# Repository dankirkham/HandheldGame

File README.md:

# HandheldGame
DOT MATRIX WITHOUT STEREO SOUND

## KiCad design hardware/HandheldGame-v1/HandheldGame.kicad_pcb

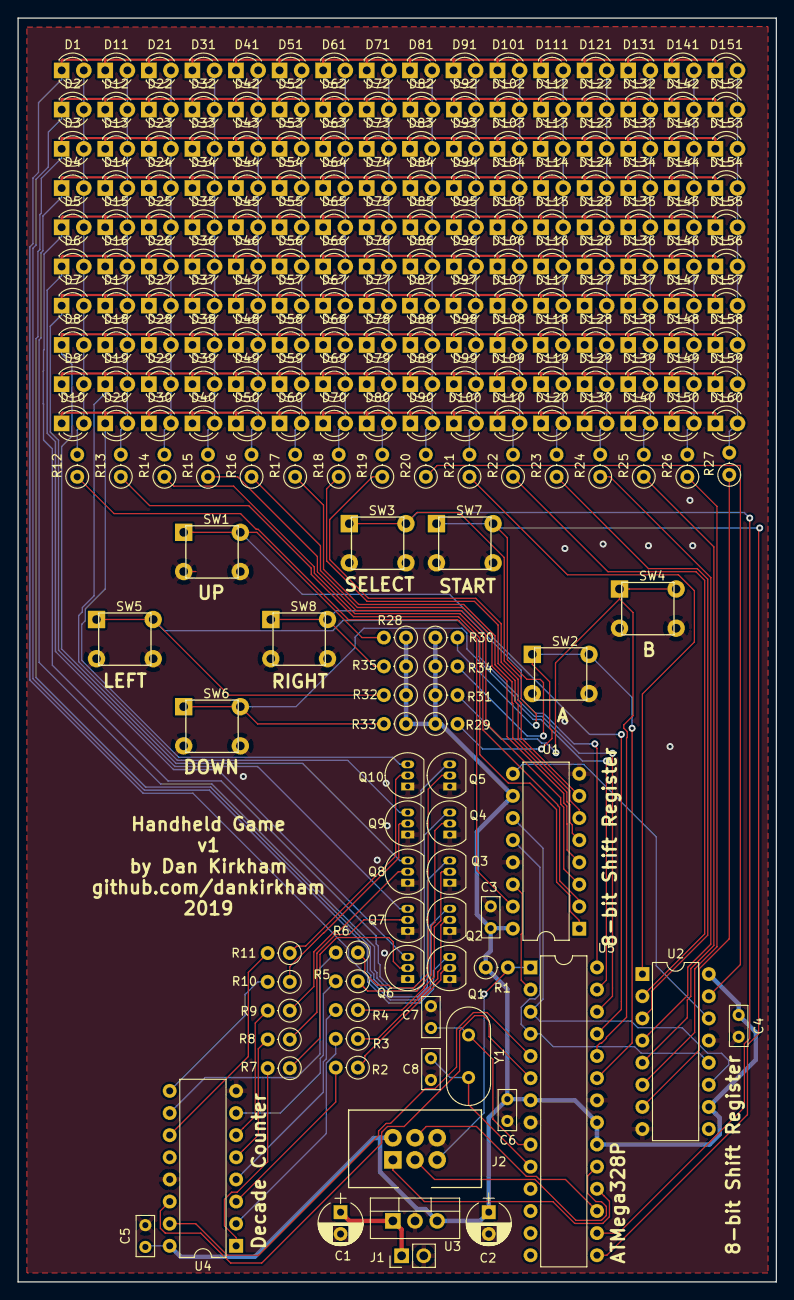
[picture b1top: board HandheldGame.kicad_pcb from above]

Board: 2 copper layers, 87.0 x 145.0 mm, 229 parts (0 on the bottom side), 85 nets.

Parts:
C1, C2: CP; CP_Radial_D5.0mm_P2.50mm
C3, C4, C5, C6: 100nF; C_Rect_L4.6mm_W2.0mm_P2.50mm_MKS02_FKP02
C7, C8: 22uF; C_Rect_L4.6mm_W2.0mm_P2.50mm_MKS02_FKP02
D1, D2, D3, D4, D5, D6, D7, D8, D9, D10, D11, D12, D13, D14, D15, D16, D17, D18, D19, D20, D21, D22, D23, D24, D25, D26, D27, D28, D29, D30, D31, D32, D33, D34, D35, D36, D37, D38, D39, D40, D41, D42, D43, D44, D45, D46, D47, D48, D49, D50, D51, D52, D53, D54, D55, D56, D57, D58, D59, D60, D61, D62, D63, D64, D65, D66, D67, D68, D69, D70, D71, D72, D73, D74, D75, D76, D77, D78, D79, D80, D81, D82, D83, D84, D85, D86, D87, D88, D89, D90, D91, D92, D93, D94, D95, D96, D97, D98, D99, D100, D101, D102, D103, D104, D105, D106, D107, D108, D109, D110, D111, D112, D113, D114, D115, D116, D117, D118, D119, D120, D121, D122, D123, D124, D125, D126, D127, D128, D129, D130, D131, D132, D133, D134, D135, D136, D137, D138, D139, D140, D141, D142, D143, D144, D145, D146, D147, D148, D149, D150, D151, D152, D153, D154, D155, D156, D157, D158, D159, D160: LED; LED_D3.0mm
J1: Conn_01x02_Male; Pin_Header_Straight_1x02_Pitch2.54mm
J2: Conn_02x03_Odd_Even; ISP_Header
Q1, Q2, Q3, Q4, Q5, Q6, Q7, Q8, Q9, Q10: 2N3904; TO-92_Inline_Narrow_Oval
R1, R28, R29, R30, R31, R32, R33, R34, R35: 10k; R_Axial_DIN0207_L6.3mm_D2.5mm_P2.54mm_Vertical
R2, R3, R4, R5, R6, R7, R8, R9, R10, R11: 2K; R_Axial_DIN0207_L6.3mm_D2.5mm_P2.54mm_Vertical
R12, R13, R14, R15, R16, R17, R18, R19, R20, R21, R22, R23, R24, R25, R26, R27: 330; R_Axial_DIN0207_L6.3mm_D2.5mm_P2.54mm_Vertical
SW1, SW2, SW3, SW4, SW5, SW6, SW7, SW8: 1825910-6
U1, U2: 74HC595; DIP-16_W7.62mm
U3: L7805; TO-220-3_Vertical
U4: CD4017BE; DIP-16_W7.62mm
U5: ATmega328P-PU; DIP-28_W7.62mm
Y1: 16MHz; Crystal_HC49-U_Vertical

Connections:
+5V: C2.1, C3.1, C4.1, C5.1, C6.1, J2.2, R1.1, R28.1, R29.1, R30.1, R31.1, R32.1, R33.1, R34.1, R35.1, U1.10, U1.16, U2.10, U2.16, U3.3, U4.16, U5.7, U5.20, U5.21
+BATT: C1.1, J1.1, U3.1
/A_BUTTON: R29.2, SW2.1, SW2.2, U5.23
/B_BUTTON: R31.2, SW4.1, SW4.2, U5.24
/DECADE_CLOCK: U4.14, U5.6
/DECADE_RESET: U4.15, U5.5
/DOWN_BUTTON: R33.2, SW6.1, SW6.2, U5.27
/LEFT_BUTTON: R32.2, SW5.1, SW5.2, U5.26
/MISO: J2.1, U5.18
/MOSI: J2.4, U5.17
/Matrix/C0: R12.1, U1.15
/Matrix/C1: R13.1, U1.1
/Matrix/C2: R14.1, U1.2
/Matrix/C3: R15.1, U1.3
/Matrix/C4: R16.1, U1.4
/Matrix/C5: R17.1, U1.5
/Matrix/C6: R18.1, U1.6
/Matrix/C7: R19.1, U1.7
/Matrix/C8: R20.1, U2.15
/Matrix/C9: R21.1, U2.1
/Matrix/C10: R22.1, U2.2
/Matrix/C11: R23.1, U2.3
/Matrix/C12: R24.1, U2.4
/Matrix/C13: R25.1, U2.5
/Matrix/C14: R26.1, U2.6
/Matrix/C15: R27.1, U2.7
/Matrix/R0: R2.2, U4.3
/Matrix/R1: R3.2, U4.2
/Matrix/R2: R4.2, U4.4
/Matrix/R3: R5.2, U4.7
/Matrix/R4: R6.2, U4.10
/Matrix/R5: R7.2, U4.1
/Matrix/R6: R8.2, U4.5
/Matrix/R7: R9.2, U4.6
/Matrix/R8: R10.2, U4.9
/Matrix/R9: R11.2, U4.11
/RESET: J2.5, R1.2, U5.1
/RIGHT_BUTTON: R35.2, SW8.1, SW8.2, U5.28
/SCK: J2.3, U5.19
/SELECT_BUTTON: R30.2, SW3.1, SW3.2, U5.16
/SHIFT_CLOCK: U1.11, U2.11, U5.3
/SHIFT_DATA: U1.14, U5.2
/SHIFT_LATCH: U1.12, U2.12, U5.4
/START_BUTTON: R34.2, SW7.1, SW7.2, U5.15
/UP_BUTTON: R28.2, SW1.1, SW1.2, U5.25
GND: C1.2, C2.2, C3.2, C4.2, C5.2, C6.2, C7.1, C8.1, J1.2, J2.6, Q1.1, Q2.1, Q3.1, Q4.1, Q5.1, Q6.1, Q7.1, Q8.1, Q9.1, Q10.1, SW1.3, SW1.4, SW2.3, SW2.4, SW3.3, SW3.4, SW4.3, SW4.4, SW5.3, SW5.4, SW6.3, SW6.4, SW7.3, SW7.4, SW8.3, SW8.4, U1.8, U1.13, U2.8, U2.13, U3.2, U4.8, U4.13, U5.8, U5.22
unnamed: C7.2, U5.9, Y1.1
unnamed: C8.2, U5.10, Y1.2
unnamed: D1.1, D11.1, D21.1, D31.1, D41.1, D51.1, D61.1, D71.1, D81.1, D91.1, D101.1, D111.1, D121.1, D131.1, D141.1, D151.1, Q1.3
unnamed: D1.2, D2.2, D3.2, D4.2, D5.2, D6.2, D7.2, D8.2, D9.2, D10.2, R12.2
unnamed: D10.1, D20.1, D30.1, D40.1, D50.1, D60.1, D70.1, D80.1, D90.1, D100.1, D110.1, D120.1, D130.1, D140.1, D150.1, D160.1, Q10.3
unnamed: D11.2, D12.2, D13.2, D14.2, D15.2, D16.2, D17.2, D18.2, D19.2, D20.2, R13.2
unnamed: D21.2, D22.2, D23.2, D24.2, D25.2, D26.2, D27.2, D28.2, D29.2, D30.2, R14.2
unnamed: D31.2, D32.2, D33.2, D34.2, D35.2, D36.2, D37.2, D38.2, D39.2, D40.2, R15.2
unnamed: D41.2, D42.2, D43.2, D44.2, D45.2, D46.2, D47.2, D48.2, D49.2, D50.2, R16.2
unnamed: D51.2, D52.2, D53.2, D54.2, D55.2, D56.2, D57.2, D58.2, D59.2, D60.2, R17.2
unnamed: D61.2, D62.2, D63.2, D64.2, D65.2, D66.2, D67.2, D68.2, D69.2, D70.2, R18.2
unnamed: D71.2, D72.2, D73.2, D74.2, D75.2, D76.2, D77.2, D78.2, D79.2, D80.2, R19.2
unnamed: D81.2, D82.2, D83.2, D84.2, D85.2, D86.2, D87.2, D88.2, D89.2, D90.2, R20.2
unnamed: D91.2, D92.2, D93.2, D94.2, D95.2, D96.2, D97.2, D98.2, D99.2, D100.2, R21.2
unnamed: D101.2, D102.2, D103.2, D104.2, D105.2, D106.2, D107.2, D108.2, D109.2, D110.2, R22.2
unnamed: D2.1, D12.1, D22.1, D32.1, D42.1, D52.1, D62.1, D72.1, D82.1, D92.1, D102.1, D112.1, D122.1, D132.1, D142.1, D152.1, Q2.3
unnamed: D3.1, D13.1, D23.1, D33.1, D43.1, D53.1, D63.1, D73.1, D83.1, D93.1, D103.1, D113.1, D123.1, D133.1, D143.1, D153.1, Q3.3
unnamed: D4.1, D14.1, D24.1, D34.1, D44.1, D54.1, D64.1, D74.1, D84.1, D94.1, D104.1, D114.1, D124.1, D134.1, D144.1, D154.1, Q4.3
unnamed: D5.1, D15.1, D25.1, D35.1, D45.1, D55.1, D65.1, D75.1, D85.1, D95.1, D105.1, D115.1, D125.1, D135.1, D145.1, D155.1, Q5.3
unnamed: D6.1, D16.1, D26.1, D36.1, D46.1, D56.1, D66.1, D76.1, D86.1, D96.1, D106.1, D116.1, D126.1, D136.1, D146.1, D156.1, Q6.3
unnamed: D7.1, D17.1, D27.1, D37.1, D47.1, D57.1, D67.1, D77.1, D87.1, D97.1, D107.1, D117.1, D127.1, D137.1, D147.1, D157.1, Q7.3
unnamed: D8.1, D18.1, D28.1, D38.1, D48.1, D58.1, D68.1, D78.1, D88.1, D98.1, D108.1, D118.1, D128.1, D138.1, D148.1, D158.1, Q8.3
unnamed: D9.1, D19.1, D29.1, D39.1, D49.1, D59.1, D69.1, D79.1, D89.1, D99.1, D109.1, D119.1, D129.1, D139.1, D149.1, D159.1, Q9.3
unnamed: D111.2, D112.2, D113.2, D114.2, D115.2, D116.2, D117.2, D118.2, D119.2, D120.2, R23.2
unnamed: D121.2, D122.2, D123.2, D124.2, D125.2, D126.2, D127.2, D128.2, D129.2, D130.2, R24.2
unnamed: D131.2, D132.2, D133.2, D134.2, D135.2, D136.2, D137.2, D138.2, D139.2, D140.2, R25.2
unnamed: D141.2, D142.2, D143.2, D144.2, D145.2, D146.2, D147.2, D148.2, D149.2, D150.2, R26.2
unnamed: D151.2, D152.2, D153.2, D154.2, D155.2, D156.2, D157.2, D158.2, D159.2, D160.2, R27.2
unnamed: Q1.2, R2.1
unnamed: Q2.2, R3.1
unnamed: Q3.2, R4.1
unnamed: Q4.2, R5.1
unnamed: Q5.2, R6.1
unnamed: Q6.2, R7.1
unnamed: Q7.2, R8.1
unnamed: Q8.2, R9.1
unnamed: Q9.2, R10.1
unnamed: Q10.2, R11.1
unnamed: U1.9, U2.14

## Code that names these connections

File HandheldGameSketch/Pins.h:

#ifndef Pins_h
#define Pins_h

#define PIN_SHIFT_DATA 0 // PD0
#define PIN_SHIFT_CLOCK 1 // PD1
#define PIN_SHIFT_LATCH 2 // PD2
#define PIN_DECADE_RESET 3 // PD3
#define PIN_DECADE_CLOCK 4 // PD4
#define PIN_BUTTON_START 9 // PB1
#define PIN_BUTTON_SELECT 10 // PB2
#define PIN_BUTTON_A A0 // PC0
#define PIN_BUTTON_B A1 // PC1
#define PIN_BUTTON_UP A2 // PC2
#define PIN_BUTTON_LEFT A3 // PC3
#define PIN_BUTTON_DOWN A4 // PC4
#define PIN_BUTTON_RIGHT A5 // PC5

#define RAW_PIN_BUTTON_START 1
#define RAW_PIN_BUTTON_SELECT 2

#define RAW_PIN_BUTTON_A 0
#define RAW_PIN_BUTTON_B 1
#define RAW_PIN_BUTTON_UP 2
#define RAW_PIN_BUTTON_LEFT 3
#define RAW_PIN_BUTTON_DOWN 4
#define RAW_PIN_BUTTON_RIGHT 5

#define ROWS 10
#define COLUMNS 16

#endif

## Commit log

2019-03-29 Initial commit of hardware and Arduino sketch.
2019-03-29 Add picture.
2020-02-27 Snake with shitty debouncing.
2020-02-28 Refactor to modules.
2020-02-29 Game over on body collision. Dont spawn appled on snek.
2020-02-29 Improved button detection/debouncing
2020-03-04 Added an enclosure.
2020-03-05 Enclosure v2.
2020-04-08 Created Makefile.
2020-04-09 Added Brick Breaker.
2020-04-09 Use LF.
2020-04-09 Ugh.
2021-12-02 Building with cmake
2021-12-04 Builds for Arduino and x86 targets.
2021-12-09 Move random to it's own header.
2021-12-09 First cut at QT
2021-12-21 Qt window with input support
2021-12-30 Fix food spawning in snake.
2021-12-31 Added test drawing.
2022-01-29 Menu to choose between games.
2022-02-13 Add Birb.
2022-03-23 Optimizations to reduce memory usage and DRY code.
2022-03-24 Remove double buffer, input debounce, and make some games faster.
2022-03-26 Experiment with shaded colors. Tighten up screen drawing code.
2022-03-27 Add Tetris. Improve button api.
2022-03-29 Optimize several const arrays to use PROGMEM on the arduino, so that they are placed in flash instead of RAM.
2022-03-31 Gui and arduino now use a common executor
2022-04-02 Add Pong
2022-04-03 Fix scroll bar on Menu. Add tetris contants to namespace. Add Quest game.
2022-04-04 Expand map, make sure entity states are persistent when the map reloads.
2022-04-05 Fix entities on real hardware.
